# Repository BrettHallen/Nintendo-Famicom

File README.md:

# Nintendo Famicom
Information regarding the Nintendo Family Computer (ニンテンドーファミリーコンピュータ) or Famicom.<br>

## [Dual PPU for Famicom](/ANES_decrazyo)
An implementation of [decrazyo's design](https://github.com/decrazyo/anes) for the NES, creating the Advanced Nintendo Entertainment System or "ANES".

## [Original Schematics](/Archive_Schematics)
Copy of the schematics from [Archive](https://archive.org/details/fc-factory-cpu-schematic-scan).

> Originally from https://forums.nesdev.org/viewtopic.php?t=6950<br>
> Recovered using the Wayback Machine.

> Here is a collection of various schematics for the Nintendo Famicom and related hardware.<br>
> Schematics were pulled from various Japanese sites and dumped onto an Atari themed vintage electronics focused website, however were "lost" when said website went down sometime between late 2017 and early 2018.<br>
> Thankfully, though, they were all backed up onto the Wayback Machine & various other sites, and just took a bit of digging to collect.<br>

> I do not know who the original creators of these schematics are, unfortunately.<br>

I'm informed that the schematics were originally drawn by [Enri](http://cmpslv3.stars.ne.jp).<br>

## [Keyboard (HVC-007)](/Keyboard_HVC-007)
Redesign of the keyboard used with Family BASIC using KiCad.<br>

## [Family BASIC (HVC-BS)](/Family_BASIC_HVC-BS)
Designing cartridge with 8KB RAM.<br>

Also includes a Python script to patch the v3 ROM to allow 8KB of RAM and also fix some bugs.<br>

- [Disassembly](https://github.com/micahcowan/fbdasm)
- [Cartridge schematics](http://cmpslv3.stars.ne.jp/Famic/Fambas.htm)
- [Leaded Solder's investigation](https://www.leadedsolder.com/2025/03/11/family-basic-space-arcade-game-programming.html)

## [3D System (HVC-032)](/3D_System_HVC-032)
Photos & schematic for the controller unit HVC-032.<br>

## [Communication Controller (HVC-051)](/Communication_Controller_HVC-051)
Japanese: 通信コントローラ<br>
Photos & schematic for the Famicom Network controller.<br>

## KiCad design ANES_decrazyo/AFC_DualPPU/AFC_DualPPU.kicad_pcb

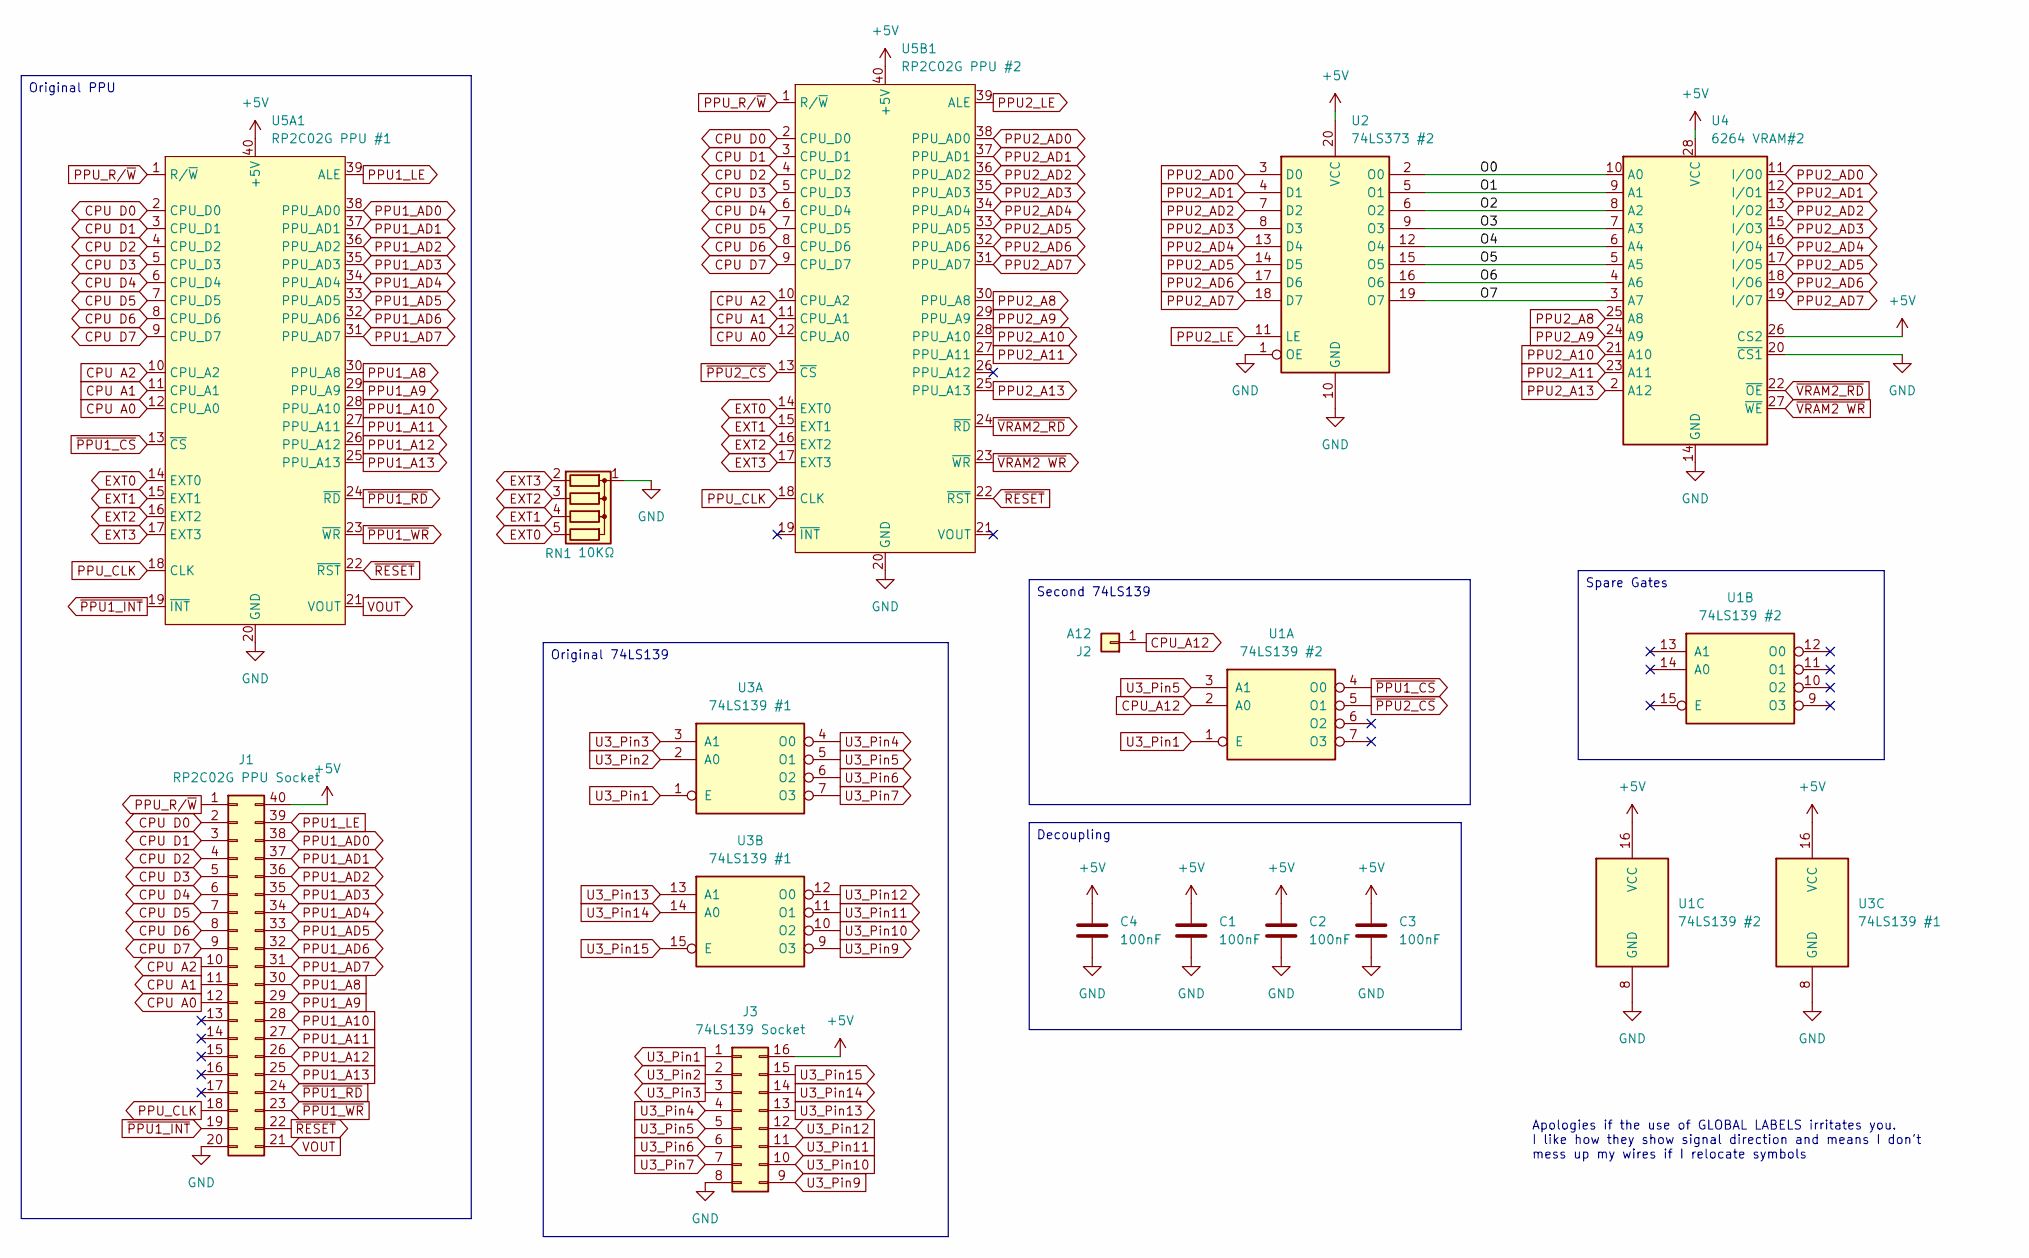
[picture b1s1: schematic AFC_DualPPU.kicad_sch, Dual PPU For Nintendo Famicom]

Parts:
C1, C2, C3, C4: 100nF; C_Disc_D3.4mm_W2.1mm_P2.50mm
J1: RP2C02G PPU Socket; DIP-40_W15.24mm
J2: A12; PinHeader_1x01_P2.54mm_Vertical
J3: 74LS139 Socket; DIP-16_W7.62mm
RN1: 10KΩ; R_Array_SIP5
U1: 74LS139 #2; DIP-16_W7.62mm
U2: 74LS373 #2; DIP-20_W7.62mm
U3: 74LS139 #1; DIP-16_W7.62mm
U4: 6264 VRAM#2; DIP-28_W15.24mm
U5A1: RP2C02G PPU #1; DIP-40_W15.24mm
U5B1: RP2C02G PPU #2; DIP-40_W15.24mm

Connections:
+5V: C1.1, C2.1, C3.1, C4.1, J1.40, J3.16, U1.16 (VCC), U2.20 (VCC), U3.16 (VCC), U4.26 (CS2), U4.28 (VCC), U5A1.40 (+5V), U5B1.40 (+5V)
/O0: U2.2 (O0), U4.10 (A0)
/O1: U2.5 (O1), U4.9 (A1)
/O2: U2.6 (O2), U4.8 (A2)
/O3: U2.9 (O3), U4.7 (A3)
/O4: U2.12 (O4), U4.6 (A4)
/O5: U2.15 (O5), U4.5 (A5)
/O6: U2.16 (O6), U4.4 (A6)
/O7: U2.19 (O7), U4.3 (A7)
CPU A0: J1.12, U5A1.12 (CPU_A0), U5B1.12 (CPU_A0)
CPU A1: J1.11, U5A1.11 (CPU_A1), U5B1.11 (CPU_A1)
CPU A2: J1.10, U5A1.10 (CPU_A2), U5B1.10 (CPU_A2)
CPU D0: J1.2, U5A1.2 (CPU_D0), U5B1.2 (CPU_D0)
CPU D1: J1.3, U5A1.3 (CPU_D1), U5B1.3 (CPU_D1)
CPU D2: J1.4, U5A1.4 (CPU_D2), U5B1.4 (CPU_D2)
CPU D3: J1.5, U5A1.5 (CPU_D3), U5B1.5 (CPU_D3)
CPU D4: J1.6, U5A1.6 (CPU_D4), U5B1.6 (CPU_D4)
CPU D5: J1.7, U5A1.7 (CPU_D5), U5B1.7 (CPU_D5)
CPU D6: J1.8, U5A1.8 (CPU_D6), U5B1.8 (CPU_D6)
CPU D7: J1.9, U5A1.9 (CPU_D7), U5B1.9 (CPU_D7)
CPU_A12: J2.1 (Pin_1_1), U1.2 (A0)
EXT0: RN1.5 (R4), U5A1.14 (EXT0), U5B1.14 (EXT0)
EXT1: RN1.4 (R3), U5A1.15 (EXT1), U5B1.15 (EXT1)
EXT2: RN1.3 (R2), U5A1.16 (EXT2), U5B1.16 (EXT2)
EXT3: RN1.2 (R1), U5A1.17 (EXT3), U5B1.17 (EXT3)
GND: C1.2, C2.2, C3.2, C4.2, J1.20, J3.8, RN1.1 (common), U1.8 (GND), U2.1 (OE), U2.10 (GND), U3.8 (GND), U4.14 (GND), U4.20 (~CS1), U5A1.20 (GND), U5B1.20 (GND)
PPU1_A8: J1.30, U5A1.30 (PPU_A8)
PPU1_A9: J1.29, U5A1.29 (PPU_A9)
PPU1_A10: J1.28, U5A1.28 (PPU_A10)
PPU1_A11: J1.27, U5A1.27 (PPU_A11)
PPU1_A12: J1.26, U5A1.26 (PPU_A12)
PPU1_A13: J1.25, U5A1.25 (PPU_A13)
PPU1_AD0: J1.38, U5A1.38 (PPU_AD0)
PPU1_AD1: J1.37, U5A1.37 (PPU_AD1)
PPU1_AD2: J1.36, U5A1.36 (PPU_AD2)
PPU1_AD3: J1.35, U5A1.35 (PPU_AD3)
PPU1_AD4: J1.34, U5A1.34 (PPU_AD4)
PPU1_AD5: J1.33, U5A1.33 (PPU_AD5)
PPU1_AD6: J1.32, U5A1.32 (PPU_AD6)
PPU1_AD7: J1.31, U5A1.31 (PPU_AD7)
PPU1_LE: J1.39, U5A1.39 (ALE)
PPU2_A8: U4.25 (A8), U5B1.30 (PPU_A8)
PPU2_A9: U4.24 (A9), U5B1.29 (PPU_A9)
PPU2_A10: U4.21 (A10), U5B1.28 (PPU_A10)
PPU2_A11: U4.23 (A11), U5B1.27 (PPU_A11)
PPU2_A13: U4.2 (A12), U5B1.25 (PPU_A13)
PPU2_AD0: U2.3 (D0), U4.11 (I/O0), U5B1.38 (PPU_AD0)
PPU2_AD1: U2.4 (D1), U4.12 (I/O1), U5B1.37 (PPU_AD1)
PPU2_AD2: U2.7 (D2), U4.13 (I/O2), U5B1.36 (PPU_AD2)
PPU2_AD3: U2.8 (D3), U4.15 (I/O3), U5B1.35 (PPU_AD3)
PPU2_AD4: U2.13 (D4), U4.16 (I/O4), U5B1.34 (PPU_AD4)
PPU2_AD5: U2.14 (D5), U4.17 (I/O5), U5B1.33 (PPU_AD5)
PPU2_AD6: U2.17 (D6), U4.18 (I/O6), U5B1.32 (PPU_AD6)
PPU2_AD7: U2.18 (D7), U4.19 (I/O7), U5B1.31 (PPU_AD7)
PPU2_LE: U2.11 (LE), U5B1.39 (ALE)
PPU_CLK: J1.18, U5A1.18 (CLK), U5B1.18 (CLK)
PPU_R/~W: J1.1, U5A1.1 (R/~W), U5B1.1 (R/~W)
U3_Pin1: J3.1, U1.1 (E), U3.1 (E)
U3_Pin2: J3.2, U3.2 (A0)
U3_Pin3: J3.3, U3.3 (A1)
U3_Pin4: J3.4, U3.4 (O0)
U3_Pin5: J3.5, U1.3 (A1), U3.5 (O1)
U3_Pin6: J3.6, U3.6 (O2)
U3_Pin7: J3.7, U3.7 (O3)
U3_Pin9: J3.9, U3.9 (O3)
U3_Pin10: J3.10, U3.10 (O2)
U3_Pin11: J3.11, U3.11 (O1)
U3_Pin12: J3.12, U3.12 (O0)
U3_Pin13: J3.13, U3.13 (A1)
U3_Pin14: J3.14, U3.14 (A0)
U3_Pin15: J3.15, U3.15 (E)
VOUT: J1.21, U5A1.21 (VOUT)
~PPU1_CS: U1.4 (O0), U5A1.13 (~CS)
~PPU1_INT: J1.19, U5A1.19 (~INT)
~PPU1_RD: J1.24, U5A1.24 (~RD)
~PPU1_WR: J1.23, U5A1.23 (~WR)
~PPU2_CS: U1.5 (O1), U5B1.13 (~CS)
~RESET: J1.22, U5A1.22 (~RST), U5B1.22 (~RST)
~VRAM2 WR: U4.27 (~WE), U5B1.23 (~WR)
~VRAM2_RD: U4.22 (~OE), U5B1.24 (~RD)

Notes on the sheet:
Apologies if the use of GLOBAL LABELS irritates you. I like how they show signal direction and means I don't mess up my wires if I relocate symbols
Original 74LS139
Second 74LS139
Decoupling
Spare Gates
Original PPU

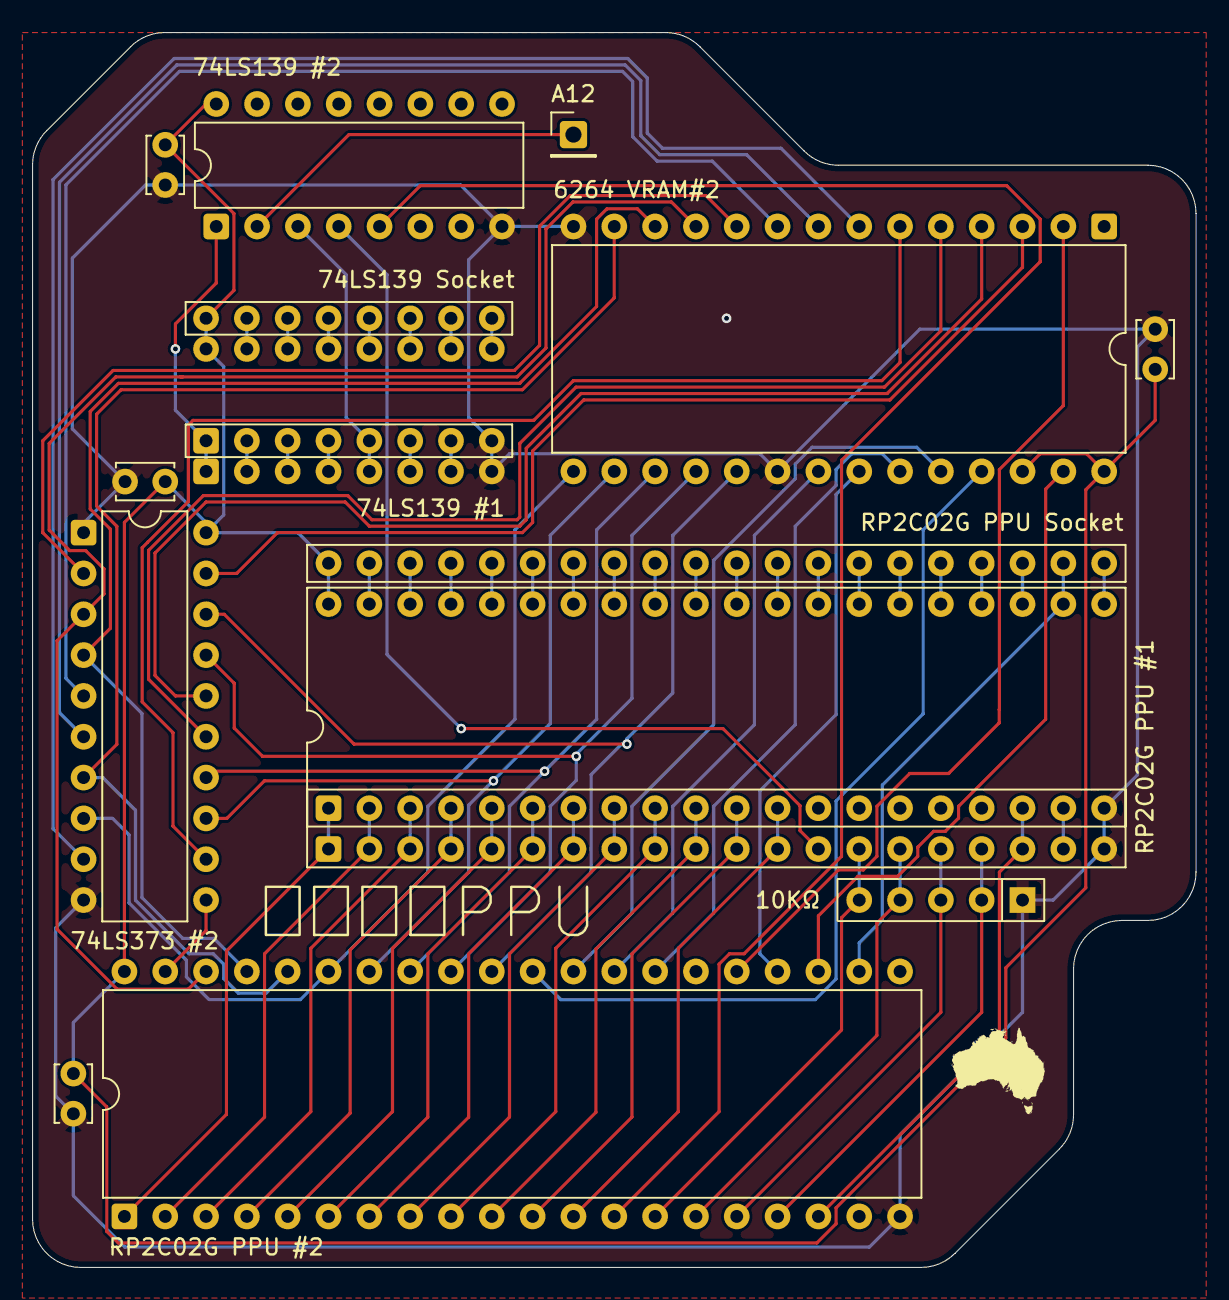
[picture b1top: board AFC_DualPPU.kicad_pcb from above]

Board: 2 copper layers, 72.4 x 76.8 mm, 14 parts (0 on the bottom side), 80 nets.

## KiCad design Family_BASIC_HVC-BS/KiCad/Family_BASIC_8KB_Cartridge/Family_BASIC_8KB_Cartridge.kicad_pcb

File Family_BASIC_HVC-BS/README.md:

# Nintendo Famicom Family BASIC

## Version 0 & 1
These are the original versions for the Famicom.<br>

I don't know much about this but I know [Mr Lurch has done a video](https://youtu.be/f1hPLmRiDNo) with v1.<br>

## Version 2.0A
- PRG: two 16KB (128Kbit) ROMs (RP2D129 0531 and RP2D129 0532) labelled "HVC-FBI-1A" and "HVC-FBI-1B"
- CHR: one 8KB (64Kbit) ROM (RP2D68 0047) labelled "HVC-FB1-0C"
- RAM: 2KB (Fujitsu MB8416A-15-SK)<br>

## Version 2.1A
This is a bugfix version that was available if you returned your v2.0A cartridge.<br>
- PRG: one 32KB (256Kbit) ROM (Fujitsu MB83256) labelled "HVC-FB1-2W"
- CHR: one 8KB (64Kbit) ROM (RP2D70 0032) labelled "HVC-FB1-0C"
- RAM: 2KB (Fujitsu MB8416A-16L-SK)

## Version 3.0
Improved BASIC with double the RAM of v2.<br>
- PRG: one 32KB (256Kbit) ROM (Toshiba TC53257P-1613) labelled "HVC-VT-0W"
- CHR: one 8KB (64Kbit) ROM (M3864-31) labelled "HVC-FB1-0C"
- RAM: 4KB (Toshiba TC5533P-B)

## Adding Support for 8KB RAM
The top of memory is hardcoded to 4KB (in v3.0) so simply replacing the 4KB (32Kbit) RAM won't make any difference - the code needs patching.<br>

There is a [information available](https://github.com/NipponNoraneko/FC-DiskBASIC) about patching v2.1A to mainly add Famicom Disk System (FDS) support, which also increases the RAM to 8KB.  This information mainly concerns itself with creating a Disk BASIC whereas I'm more interested in purely upgrading the cartridge.<br>

This [disassembly of the v3.0 ROM](https://github.com/micahcowan/fbdasm) is invaluable.<br>

So far it looks like these are the required patches in the v3.0 ROM to increase the top of RAM from 0x6FFF (4KB) to 0x7FFF (8KB) - working on verifying the others:<br>
```
   bgGetRam  .eq $6c00  {addr/1024} ; region to save bg data with BGGET
   memoryTop .eq $6fff              ; What FRETOP is set to by default

PATCH0: lda #>memoryTop
06A4: 6F -> 7F

PATCH1: cmp #$70 ;arg >= #$7000?
17D8: 70 -> 80

PATCH2: lda #(>memoryTop)+1
2DC9: 70 -> 80

PATCH3: cmp #>bgGetRam ;is there room after program for BG data?
31BE: 6C -> 7C     

PATCH4: lda #>bgGetRam
31CB: 6C -> 7C

PATCH5: lda #>bgGetRam
320C: 6C -> 7C
```

I am working on a Python script to make this patching of the binary ROM simple:<br>
```
% python3 fb_rom_patcher.py Family_BASIC_v30_PRG_CHR.NES

#############################################
# Brett's Nintendo Family BASIC ROM patcher #
# for 8KB RAM Support (Jan 2026)            #
#############################################

>> Input ROM checksum: 0x6BA08175
>> Detected: Family BASIC v3.0 (PRG+CHR+NES 2.0 header)

>> Applying single-byte patches:
Patching 0x000A: 0x60 → 0x70 [NES 2.0 header 4KB->8KB]
Patching 0x06B4: 0x6F → 0x7F [Increase RAM limit from 0x6C00 to 0x7C00]
Patching 0x17E8: 0x70 → 0x80 [Increase RAM limit from 0x6C00 to 0x7C00]
Patching 0x2DD9: 0x70 → 0x80 [Increase RAM limit from 0x6C00 to 0x7C00]
Patching 0x31CE: 0x6C → 0x7C [Increase RAM limit from 0x6C00 to 0x7C00]
Patching 0x31DB: 0x6C → 0x7C [Increase RAM limit from 0x6C00 to 0x7C00]
Patching 0x321C: 0x6C → 0x7C [Increase RAM limit from 0x6C00 to 0x7C00]
Patching 0x133E: 0xA0 → 0xA9 [REM statement bug fix]
Patching 0x4F99: 0x30 → 0x31 [Version change to v3.1]

>> Applying multi-byte patches:
Patching 0x0CAD: 0xA5 → 0xA5 [RENUM command bug fix]
Patching 0x0CAE: 0x7D → 0x7C [RENUM command bug fix]
Patching 0x0CAF: 0xC5 → 0x38 [RENUM command bug fix]
Patching 0x0CB0: 0x7F → 0xE5 [RENUM command bug fix]
Patching 0x0CB1: 0xF0 → 0x7E [RENUM command bug fix]
Patching 0x0CB2: 0x02 → 0xA5 [RENUM command bug fix]
Patching 0x0CB3: 0xB0 → 0x7D [RENUM command bug fix]
Patching 0x0CB4: 0x0C → 0xE5 [RENUM command bug fix]
Patching 0x0CB5: 0xA5 → 0x7F [RENUM command bug fix]
Patching 0x0CB6: 0x7C → 0xB0 [RENUM command bug fix]
Patching 0x0CB7: 0xC5 → 0x09 [RENUM command bug fix]
Patching 0x0CB8: 0x7E → 0x4C [RENUM command bug fix]
Patching 0x0CB9: 0xB0 → 0xAB [RENUM command bug fix]
Patching 0x0CBA: 0x06 → 0x8C [RENUM command bug fix]
Patching 0x0E52: 0x10 → 0x30 [-32768-0 overflow error bug fix]
Patching 0x0E53: 0x06 → 0x04 [-32768-0 overflow error bug fix]

>> Patched ROM saved as: Family_BASIC_v30_PRG_CHR_patched.NES
>> Patched ROM checksum: 0xEFDACFF8
>> SUCCESS: Checksum verified
```

## NES 2.0 Headers
Required to be prepended to the combined PRG+CHR ROM image to run in an emulator.<br>
I've added what *I think* are the correct NES 2.0 headers to my ROMs, and the CRC32 checksum calculation my script checks assumes these.<br>
```
% python3 nes_header_read.py Family_BASIC_v30_PRG_CHR.NES 

#################################
# Brett's NES Header Reader     #
# Work in progress, 14/JAN/2026 #
#################################

Format ............................ NES 2.0
Vs. System PPU variant ............ 0
Vs. System hardware/protection .... 0
PRG-ROM size ...................... 32768 bytes
CHR-ROM size ...................... 8192 bytes
PRG-RAM (volatile) size ........... 0 bytes
PRG-NVRAM (battery-backed) size ... 4096 bytes
CHR-RAM (volatile) size ........... 0 bytes
CHR-NVRAM (battery-backed) size ... 0 bytes
Mapper ............................ 0 (NROM)
Submapper ......................... 0
Mirroring ......................... Vertical
Battery-backed .................... True
Trainer ........................... False
Four-screen VRAM .................. False
VS Unisystem ...................... False
PlayChoice-10 ..................... False
CPU/PPU Timing .................... RP2C02 (NTSC NES)
Default expansion device .......... Family BASIC Keyboard plus Famicom Data Recorder
```

If yours are different and my script rejects your .NES file, just modify the script with the checksum it calculates for your file!<br>
```
KNOWN_CRCS = {
    "FBv10":        (0x868FCD89, 0x00000000), # no 8KB patch planned
    "FBv10_merge":  (0xF7DB8B5C, 0x00000000), # no 8KB patch planned
    "FBv10_NES":    (0x30B1840A, 0x00000000), # no 8KB patch planned
    "FBv20A_merge": (0xF7606810, 0x00000000), # no 8KB patch planned
    "FBv20A_NES2":  (0x300A6746, 0x00000000), # no 8KB patch planned
    "FBv21A":       (0xDE34526E, 0x85BDD21B), # PRG
    "FBv21A_merge": (0x895037BC, 0x72C38E25), # PRG+CHR
    "FBv21A_NES2":  (0x4E3A38EA, 0x3D43C6D0), # PRG+CHR+NES header
    "FBv30":        (0x3AAEED3F, 0xC7FD9017), # PRG
    "FBv30_merge":  (0xB2530AFC, 0x933709F7), # PRG+CHR
    "FBv30_NES2":   (0x6BA08175, 0xEFDACFF8), # PRG+CHR+NES header
    "FB_CHR":       (0x11848B93, 0x00000000)  # CHR
}
```
The checksum for the raw ROM files *should* be correct.<br>

- Family BASIC v2.1 2KB header: 4E 45 53 1A 02 01 03 08 00 00 50 00 00 00 00 23
- Family BASIC v2.1 8KB header: 4E 45 53 1A 02 01 03 08 00 00 70 00 00 00 00 23 (?)
- Family BASIC v3.0 4KB header: 4E 45 53 1A 02 01 03 08 00 00 60 00 00 00 00 23
- Family BASIC v3.0 8KB header: 4E 45 53 1A 02 01 03 08 00 00 70 00 00 00 00 23 (?)

## Version 3.0 Bugfixes
There are [several bugs](https://github.com/micahcowan/fbdasm/blob/main/BUGS.md) in v3 that have been identified.<br>

### [REM Comments Corrupted by Katakana Small Yo (ョ)](https://github.com/micahcowan/fbdasm/blob/main/BUGS.md#rem-comments-corrupted-by-katakana-small-yo-ョ) 
As noted by Micah in his [annotated disassembly](https://famibe.addictivecode.org/disassembly/fb3.nes.html):<br>
Original fault - キョートー　becomes キートー
```
932E: A0 00        TokRemCopyToEnd LDY     #$00                    ;BUG: this should be lda
9330: 85 99                        STA     zpToken                 ;...or else this should be sty
9332: 4C C2 92                     JMP     TokCopyUntilTok
```

Possible fix
```
932E: A9 00        TokRemCopyToEnd LDA     #$00                    ;LDY -> LDA
9330: 85 99                        STA     zpToken
9332: 4C C2 92                     JMP     TokCopyUntilTok
```

### [RENUM Can Create Duplicate Line Numbers](https://github.com/micahcowan/fbdasm/blob/main/BUGS.md#renum-can-create-duplicate-line-numbers)
Original fault
```
                   RENUM_checkNewGeOld
8C9D: A5 7D                        LDA     vZpNewStartLNum+1
8C9F: C5 7F                        CMP     vZpOldStartLNum+1
8CA1: F0 02                        BEQ     @cmpLo              ;is new start lnum (hi byte) > old start lnum (hi byte)?
8CA3: B0 0C                        BCS     RENUM_argsDone      ;yes -> everything's great
8CA5: A5 7C        @cmpLo          LDA     vZpNewStartLNum     ;else, is new start lnum (lo byte) >= old start lnum (lo byte)?
8CA7: C5 7E                        CMP     vZpOldStartLNum     ;BUG! Permits high byte lower, as long as low byte is higher!
8CA9: B0 06                        BCS     RENUM_argsDone      ; This can result in repeated line numbers, and/or lower coming after higher
8CAB: 4C 94 84                     JMP     ErrorIllegalValue
```

Possible fix - treat line numbers as 16-bit numbers:
```
                   RENUM_checkNewGeOld
8C9D: A5 7C                        LDA     vZpNewStartLNum     ; Load new low byte
8C9F: 38                           SEC                         ; Set carry for subtraction
8CA0: E5 7E                        SBC     vZpOldStartLNum     ; Subtract old low byte
8CA2: A5 7D                        LDA     vZpNewStartLNum+1   ; Load new high byte
8CA4: E5 7F                        SBC     vZpOldStartLNum+1   ; Subtract old high byte (with borrow)
8CA6: B0 09                        BCS     RENUM_argsDone      ; If carry set (new >= old), good –> jump to $8CB1
8CA8: 4C AB 8C                     JMP     $8CAB               ; Else error (Illegal quantity at $8CAB)
8CAB: 4C 94 84                     JMP     ErrorIllegalValue
```
(replace $8CA8 with 3xNOP and let it fall through to $8CAB?)

### [Overflow When Subtracting Zero](https://github.com/micahcowan/fbdasm/blob/main/BUGS.md#overflow-when-subtracting-zero)
Incorrect overflow (OV) error is raised when -32768-0 is executed.<br>
```
                   Sub_WAccumIs32768
8E40: A5 2D                        LDA     zpWParam+1
8E42: 10 06                        BPL     @errOverfl     ;BUG: produces OV ERROR even if WParam is zero lol
8E44: 20 FD 8D                     JSR     WParamNegate
8E47: 4C AC 8E                     JMP     Add
8E4A: 4C F2 8E     @errOverfl      JMP     ErrorOverflow
```

Possible fix - raise overflow error only when subtracting positive number (>0)
```
                   Sub_WAccumIs32768
8E40: A5 2D                        LDA     zpWParam+1
8E42: 30 04                        BMI     continue       ;if subtracting negative number, safe -> negate & add
8E44: 20 FD 8D                     JSR     WParamNegate
8E47: 4C AC 8E     continue        JMP     Add
8E4A: 4C F2 8E     @errOverfl      JMP     ErrorOverflow
```

- If subtracting negative number ... correct (negate then add)
- If subtracting zero ... doesn't branch ... falls through to Add
- If subtracting positive number... falls through to ErrorOverflow

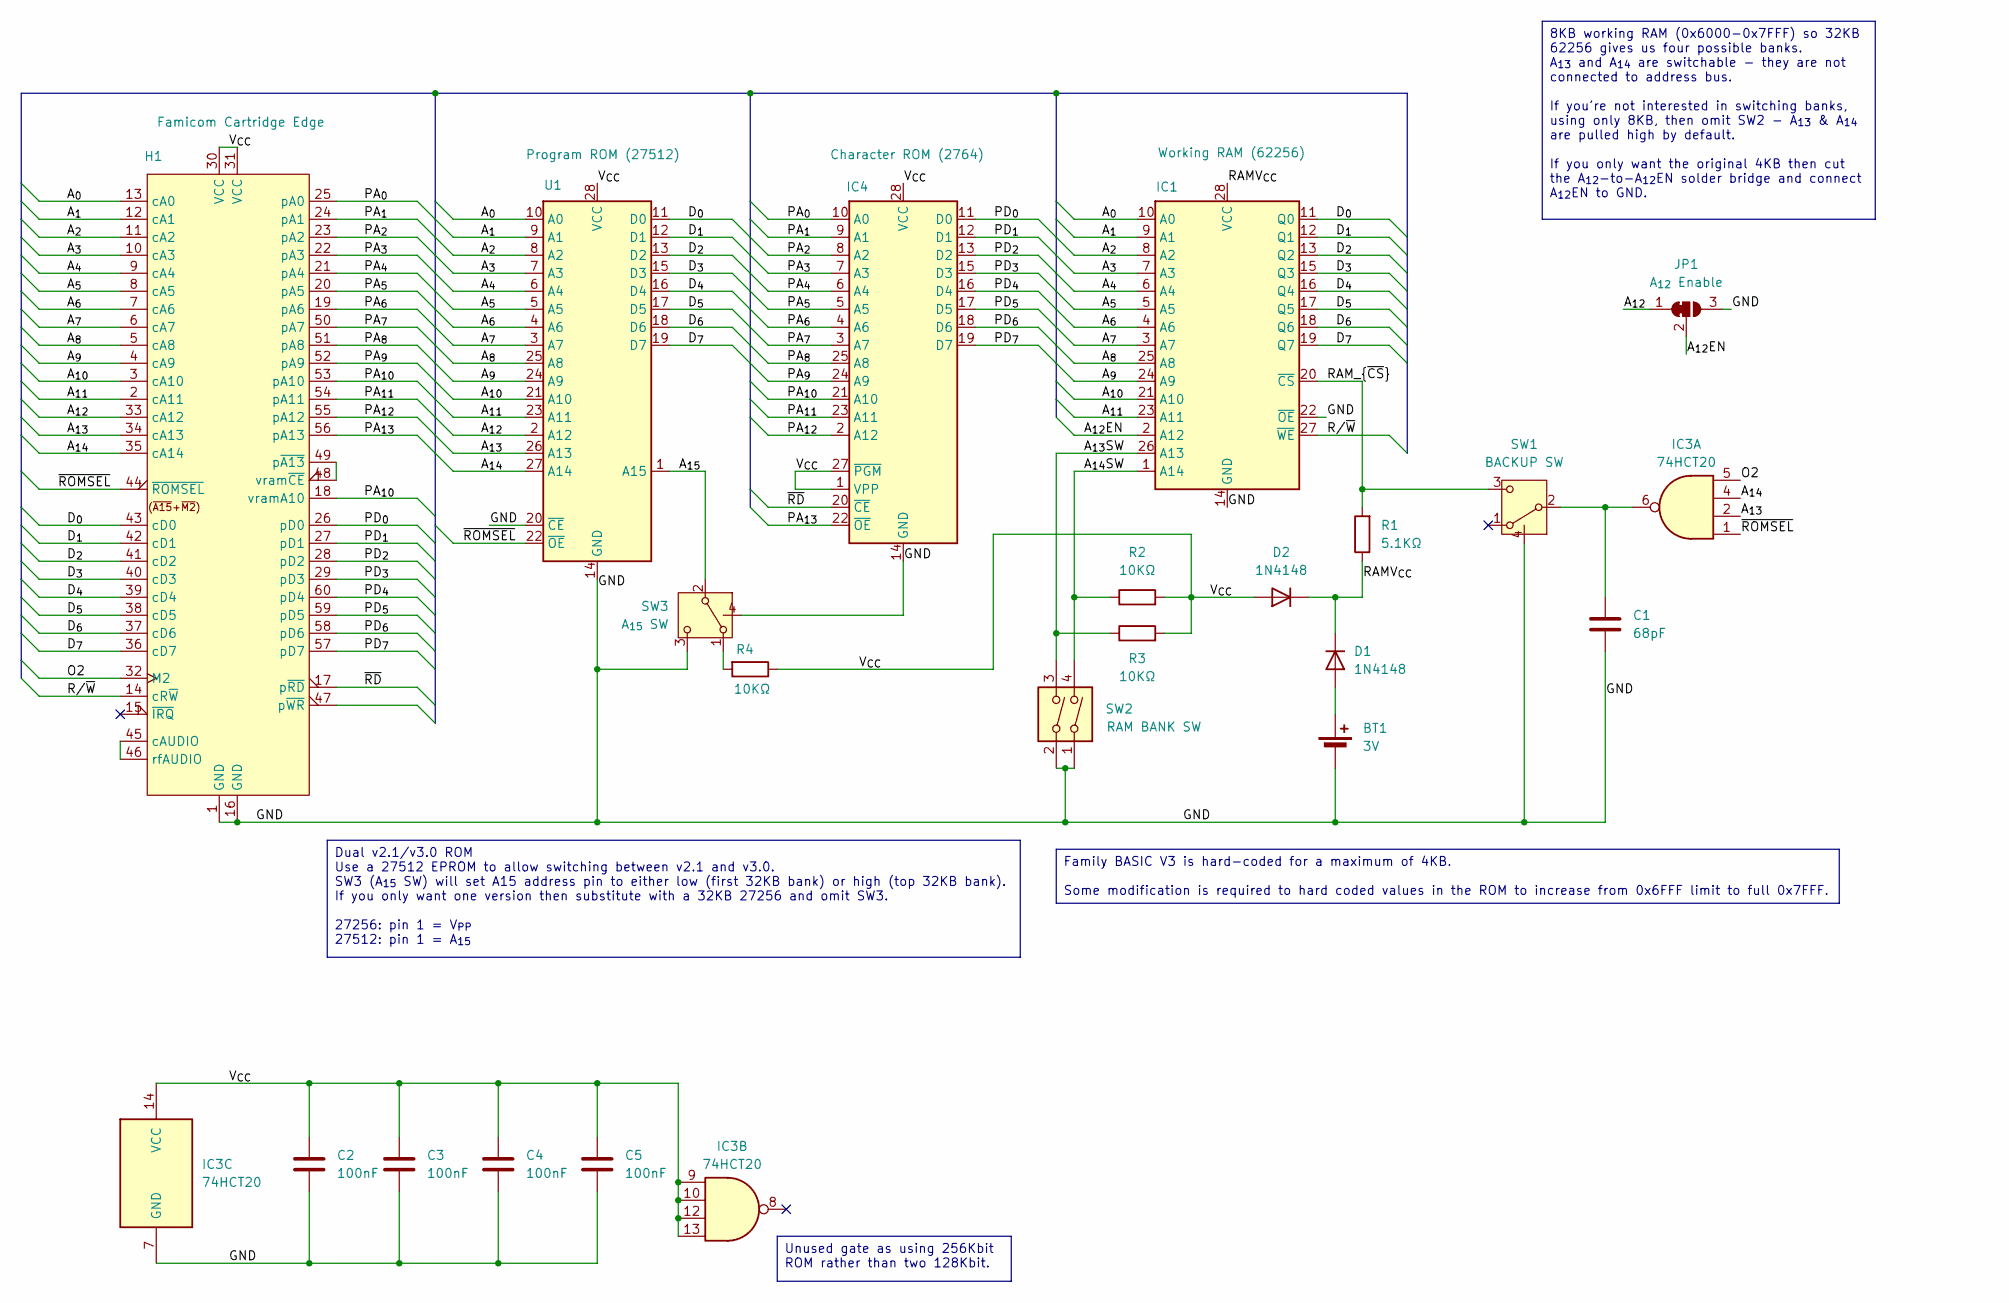
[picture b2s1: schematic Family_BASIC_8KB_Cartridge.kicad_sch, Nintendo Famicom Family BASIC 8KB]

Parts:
BT1: 3V; 3000
C1: 68pF; C_Axial_L3.8mm_D2.6mm_P7.50mm_Horizontal
C2, C3, C4, C5: 100nF; C_Axial_L3.8mm_D2.6mm_P7.50mm_Horizontal
D1, D2: 1N4148; D_DO-35_SOD27_P7.62mm_Horizontal
H1: Famicom Cartridge Edge; Famicom_Cartridge_Edge_Connector_(long_legs)
IC1: Working RAM (62256); DIP-28_W15.24mm
IC3: 74HCT20; DIP-14_W7.62mm
IC4: Character ROM (2764); DIP-28_W15.24mm
JP1: A_{12} Enable; SolderJumper-3_P1.3mm_Bridged12_RoundedPad1.0x1.5mm
R1: 5.1KΩ; R_Axial_DIN0207_L6.3mm_D2.5mm_P7.62mm_Horizontal
R2, R3, R4: 10KΩ; R_Axial_DIN0207_L6.3mm_D2.5mm_P7.62mm_Horizontal
SW1: BACKUP SW; SW_E-Switch_EG1224_SPDT_Angled
SW2: RAM BANK SW; SW_DIP_SPSTx02_Slide_9.78x7.26mm_W7.62mm_P2.54mm
SW3: A_{15} SW; SW_E-Switch_EG1224_SPDT_Angled
U1: Program ROM (27512); DIP-28_W15.24mm

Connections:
/A_{0}: H1.13 (cA0), IC1.10 (A0), U1.10 (A0)
/A_{1}: H1.12 (cA1), IC1.9 (A1), U1.9 (A1)
/A_{2}: H1.11 (cA2), IC1.8 (A2), U1.8 (A2)
/A_{3}: H1.10 (cA3), IC1.7 (A3), U1.7 (A3)
/A_{4}: H1.9 (cA4), IC1.6 (A4), U1.6 (A4)
/A_{5}: H1.8 (cA5), IC1.5 (A5), U1.5 (A5)
/A_{6}: H1.7 (cA6), IC1.4 (A6), U1.4 (A6)
/A_{7}: H1.6 (cA7), IC1.3 (A7), U1.3 (A7)
/A_{8}: H1.5 (cA8), IC1.25 (A8), U1.25 (A8)
/A_{9}: H1.4 (cA9), IC1.24 (A9), U1.24 (A9)
/A_{10}: H1.3 (cA10), IC1.21 (A10), U1.21 (A10)
/A_{11}: H1.2 (cA11), IC1.23 (A11), U1.23 (A11)
/A_{12}: H1.33 (cA12), JP1.1 (A), U1.2 (A12)
/A_{12}EN: IC1.2 (A12), JP1.2 (C)
/A_{13}: H1.34 (cA13), IC3.2, U1.26 (A13)
/A_{13}SW: IC1.26 (A13), R3.1, SW2.3
/A_{14}: H1.35 (cA14), IC3.4, U1.27 (A14)
/A_{14}SW: IC1.1 (A14), R2.1, SW2.4
/A_{15}: SW3.2 (B), U1.1 (A15)
/D_{0}: H1.43 (cD0), IC1.11 (Q0), U1.11 (D0)
/D_{1}: H1.42 (cD1), IC1.12 (Q1), U1.12 (D1)
/D_{2}: H1.41 (cD2), IC1.13 (Q2), U1.13 (D2)
/D_{3}: H1.40 (cD3), IC1.15 (Q3), U1.15 (D3)
/D_{4}: H1.39 (cD4), IC1.16 (Q4), U1.16 (D4)
/D_{5}: H1.38 (cD5), IC1.17 (Q5), U1.17 (D5)
/D_{6}: H1.37 (cD6), IC1.18 (Q6), U1.18 (D6)
/D_{7}: H1.36 (cD7), IC1.19 (Q7), U1.19 (D7)
/GND: BT1.3 (-), C1.2, C2.2, C3.2, C4.2, C5.2, H1.1 (GND), H1.16 (GND), IC1.14 (GND), IC1.22 (~OE), IC3.7 (GND), IC4.14 (GND), JP1.3 (B), SW1.4 (GND), SW2.1, SW2.2, SW3.3 (C), SW3.4 (GND), U1.14 (GND), U1.20 (~CE)
/O2: H1.32 (M2), IC3.5
/PA_{0}: H1.25 (pA0), IC4.10 (A0)
/PA_{1}: H1.24 (pA1), IC4.9 (A1)
/PA_{2}: H1.23 (pA2), IC4.8 (A2)
/PA_{3}: H1.22 (pA3), IC4.7 (A3)
/PA_{4}: H1.21 (pA4), IC4.6 (A4)
/PA_{5}: H1.20 (pA5), IC4.5 (A5)
/PA_{6}: H1.19 (pA6), IC4.4 (A6)
/PA_{7}: H1.50 (pA7), IC4.3 (A7)
/PA_{8}: H1.51 (pA8), IC4.25 (A8)
/PA_{9}: H1.52 (pA9), IC4.24 (A9)
/PA_{10}: H1.18 (vramA10), H1.53 (pA10), IC4.21 (A10)
/PA_{11}: H1.54 (pA11), IC4.23 (A11)
/PA_{12}: H1.55 (pA12), IC4.2 (A12)
/PA_{13}: H1.56 (pA13), IC4.22 (~OE)
/PD_{0}: H1.26 (pD0), IC4.11 (D0)
/PD_{1}: H1.27 (pD1), IC4.12 (D1)
/PD_{2}: H1.28 (pD2), IC4.13 (D2)
/PD_{3}: H1.29 (pD3), IC4.15 (D3)
/PD_{4}: H1.60 (pD4), IC4.16 (D4)
/PD_{5}: H1.59 (pD5), IC4.17 (D5)
/PD_{6}: H1.58 (pD6), IC4.18 (D6)
/PD_{7}: H1.57 (pD7), IC4.19 (D7)
/RAMV_{CC}: D1.1 (K), D2.1 (K), IC1.28 (VCC), R1.1
/RAM_{~CS}: IC1.20 (~CS), R1.2, SW1.3 (C)
/R/~W: H1.14 (cR~W), IC1.27 (~WE)
/V_{CC}: C2.1, C3.1, C4.1, C5.1, D2.2 (A), H1.30 (VCC), H1.31 (VCC), IC3.9, IC3.10, IC3.12, IC3.13, IC3.14 (VCC), IC4.1 (VPP), IC4.27 (~PGM), IC4.28 (VCC), R2.2, R3.2, R4.1, U1.28 (VCC)
/~RD: H1.17 (p~RD), IC4.20 (~CE)
/~ROMSEL: H1.44 (~ROMSEL), IC3.1, U1.22 (~OE)
unnamed: BT1.1 (+), D1.2 (A)
unnamed: H1.45 (cAUDIO), H1.46 (rfAUDIO)
unnamed: H1.48 (vram~CE), H1.49 (p~A13)
unnamed: C1.1, IC3.6, SW1.2 (B)
unnamed: R4.2, SW3.1 (A)

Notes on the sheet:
Dual v2.1/v3.0 ROM Use a 27512 EPROM to allow switching between v2.1 and v3.0. SW3 (A_{15} SW) will set A15 address pin to either low (first 32KB bank) or high (top 32KB bank). If you only want one version then substitute with a 32KB 27256 and omit SW3. 27256: pin 1 = V_{PP} 27512: pin 1 = A_{15}
Unused gate as using 256Kbit ROM rather than two 128Kbit.
8KB working RAM (0x6000-0x7FFF) so 32KB 62256 gives us four possible banks. A_{13} and A_{14} are switchable - they are not connected to address bus. If you're not interested in switching banks, using only 8KB, then omit SW2 - A_{13} & A_{14} are pulled high by default. If you only want the origina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
Family BASIC V3 is hard-coded for a maximum of 4KB. Some modification is required to hard coded values in the ROM to increase from 0x6FFF limit to full 0x7FFF.

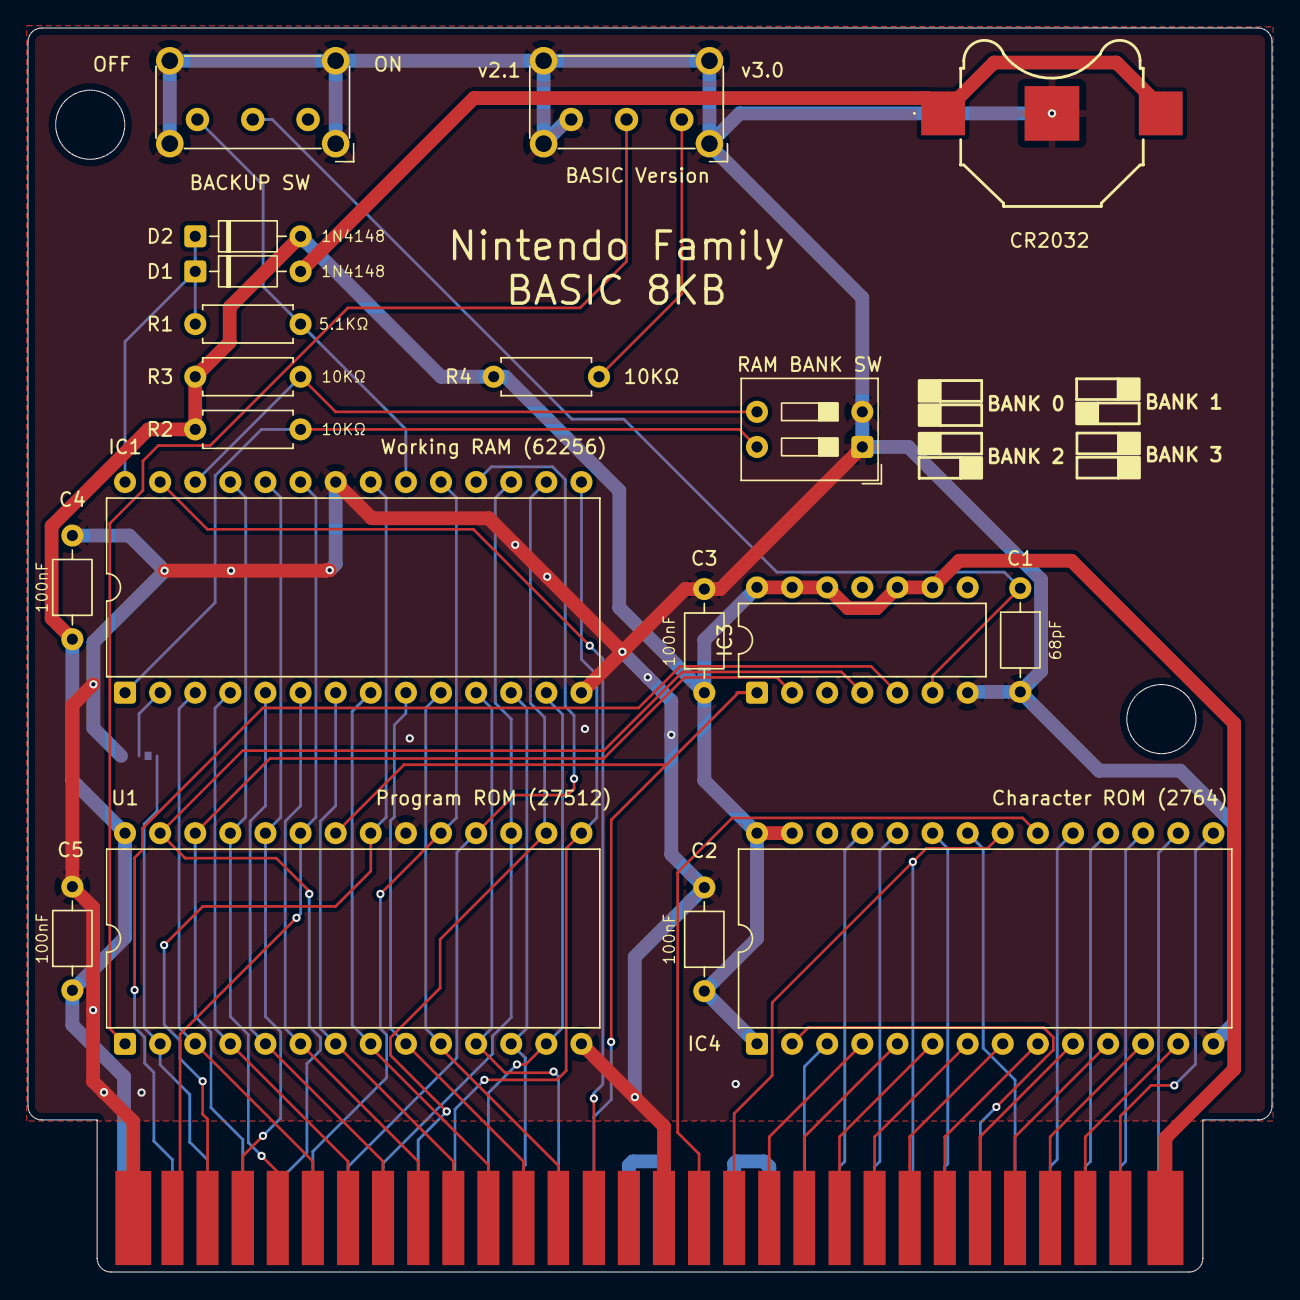
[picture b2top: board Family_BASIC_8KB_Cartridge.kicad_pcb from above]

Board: 2 copper layers, 90.0 x 90.0 mm, 21 parts (1 on the bottom side), 62 nets.

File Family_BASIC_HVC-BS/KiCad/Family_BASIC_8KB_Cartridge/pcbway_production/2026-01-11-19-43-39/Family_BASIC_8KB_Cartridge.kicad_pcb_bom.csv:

Designator,Quantity,Value,Footprint,Package,MPN,DNP,Mount_Type,Description,Sim.Device,Sim.Pins
BT1,1,3V,3000,,,,smt,Single-cell battery,,
C1,1,68pF,C_Axial_L3.8mm_D2.6mm_P7.50mm_Horizontal,,,,tht,Unpolarized capacitor,,
"C2, C3, C4, C5",4,100nF,C_Axial_L3.8mm_D2.6mm_P7.50mm_Horizontal,,,,tht,Unpolarized capacitor,,
"D1, D2",2,1N4148,D_DO-35_SOD27_P7.62mm_Horizontal,,,,tht,Diode,D,1=K 2=A
H1,1,Famicom Cartridge Edge,Famicom_Cartridge_Edge_Connector_(long_legs),,,,smt,,,
IC1,1,Working RAM (62256),DIP-28_W15.24mm,,,,tht,"32,768-word × 8-bit High Speed CMOS Static RAM, 70ns, DIP-28",,
IC3,1,74HCT20,DIP-14_W7.62mm,,,,tht,Dual 4-input NAND,,
IC4,1,Character ROM (2764),DIP-28_W15.24mm,,,,tht,"OTP EPROM 64 KiBit, [Obsolete 2004-01]",,
R1,1,5.1KΩ,R_Axial_DIN0207_L6.3mm_D2.5mm_P7.62mm_Horizontal,,,,tht,Resistor,,
"R2, R3, R4",3,10KΩ,R_Axial_DIN0207_L6.3mm_D2.5mm_P7.62mm_Horizontal,,,,tht,Resistor,,
SW1,1,BACKUP SW,SW_E-Switch_EG1224_SPDT_Angled,,,,tht,"Switch, single pole double throw",,
SW2,1,RAM BANK SW,SW_DIP_SPSTx02_Slide_9.78x7.26mm_W7.62mm_P2.54mm,,,,tht,"2x DIP Switch, Single Pole Single Throw (SPST) switch, small symbol",,
SW3,1,A_{15} SW,SW_E-Switch_EG1224_SPDT_Angled,,,,tht,"Switch, single pole double throw",,
U1,1,Program ROM (27512),DIP-28_W15.24mm,,,,tht,OTP EPROM 512 KiBit,,

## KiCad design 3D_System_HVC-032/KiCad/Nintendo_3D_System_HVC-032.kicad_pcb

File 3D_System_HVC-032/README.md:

# 3D System (3DS) HVC-032

## [KiCad](/3D_System_HVC-032/KiCad)
Schematic of the 3DS controller box in KiCad.<br>

The controller uses a custom Sharp IX0043 chip.<br>

Its functionality could perhaps be replacated by an Atmega328.<br>

## [Logic Analyser](/3D_System_HVC-032/Logic_Analyser)
Capture of the controller signalling.  <br>

You can use the Saleaea Logic 2 software [(free download, no need to have the hardware)](https://saleae.com) to open the .SAL capture file.

## [Home Brew Controller](/3D_System_HVC-032/HOME-brewed_Control_Circuit)
Controller design from 1993 to use the similar Sega Master System (SMS) 3D glasses on a PC.<br>

I've not finished re-drawing in KiCad yet (11/Jan/2026).<br>

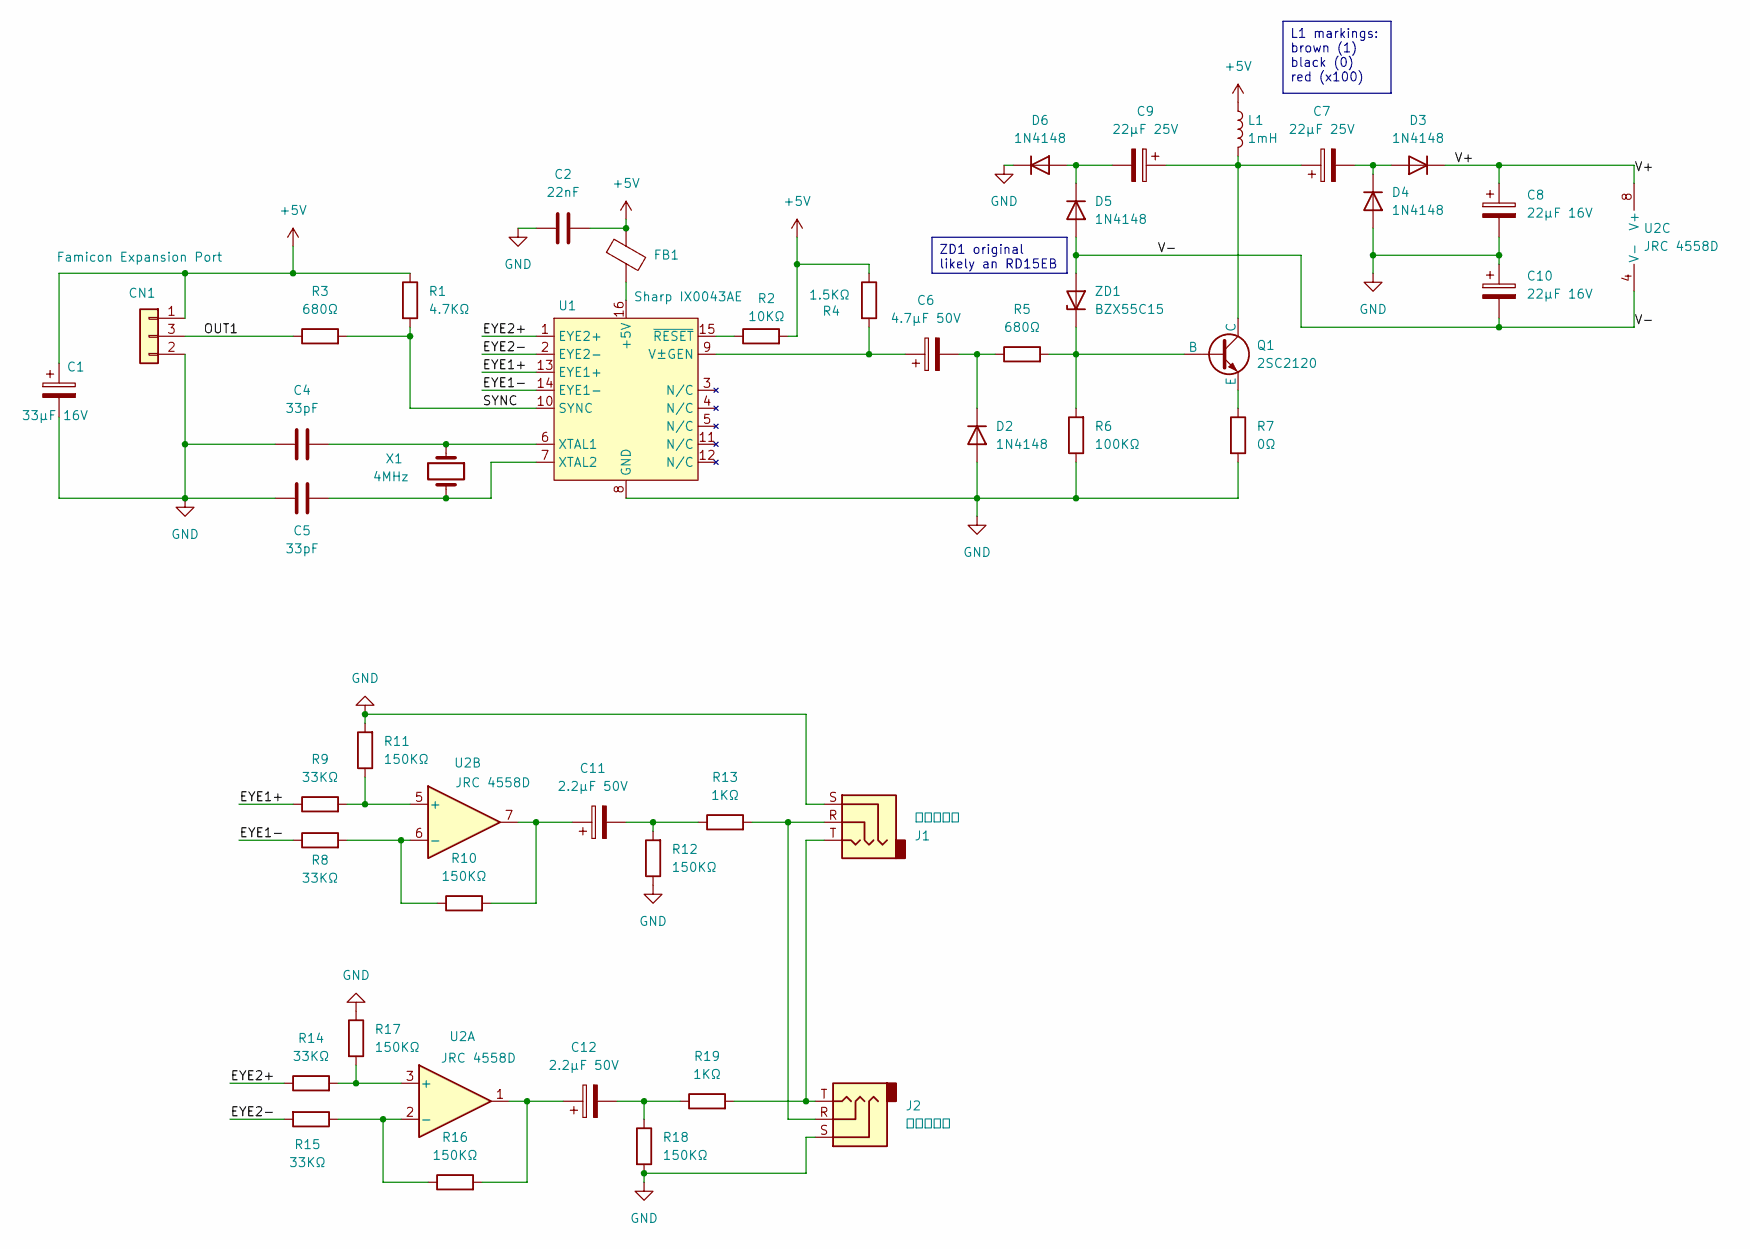
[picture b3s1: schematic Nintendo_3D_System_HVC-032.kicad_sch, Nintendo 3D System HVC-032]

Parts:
C1: 33µF 16V; CP_Radial_D5.0mm_P2.50mm
C2: 22nF; C_Disc_D3.4mm_W2.1mm_P2.50mm
C4, C5: 33pF; C_Disc_D3.4mm_W2.1mm_P2.50mm
C6: 4.7µF 50V; CP_Radial_D5.0mm_P2.50mm
C7, C9: 22µF 25V; CP_Radial_D5.0mm_P2.50mm
C8, C10: 22µF 16V; CP_Radial_D5.0mm_P2.50mm
C11, C12: 2.2µF 50V; CP_Radial_D5.0mm_P2.50mm
CN1: Famicon Expansion Port; PinHeader_1x03_P2.54mm_Vertical
D2, D3, D4, D5, D6: 1N4148; D_DO-35_SOD27_P7.62mm_Horizontal
FB1: FerriteBead; FB_28L0138-10R-10
J1: スコープ１; Jack_3.5mm_CUI_SJ1-3513N_Horizontal
J2: スコープ２; Jack_3.5mm_CUI_SJ1-3513N_Horizontal
L1: 1mH; L_Axial_L16.0mm_D7.5mm_P25.40mm_Horizontal_Fastron_XHBCC
Q1: 2SC2120; TO-92_Inline
R1: 4.7KΩ; R_Axial_DIN0207_L6.3mm_D2.5mm_P7.62mm_Horizontal
R2: 10KΩ; R_Axial_DIN0207_L6.3mm_D2.5mm_P7.62mm_Horizontal
R3, R5: 680Ω; R_Axial_DIN0207_L6.3mm_D2.5mm_P7.62mm_Horizontal
R4: 1.5KΩ; R_Axial_DIN0207_L6.3mm_D2.5mm_P7.62mm_Horizontal
R6: 100KΩ; R_Axial_DIN0207_L6.3mm_D2.5mm_P7.62mm_Horizontal
R7: 0Ω; R_Axial_DIN0207_L6.3mm_D2.5mm_P7.62mm_Horizontal
R8, R9, R14, R15: 33KΩ; R_Axial_DIN0207_L6.3mm_D2.5mm_P7.62mm_Horizontal
R10, R11, R12, R16, R17, R18: 150KΩ; R_Axial_DIN0207_L6.3mm_D2.5mm_P7.62mm_Horizontal
R13, R19: 1KΩ; R_Axial_DIN0207_L6.3mm_D2.5mm_P7.62mm_Horizontal
U1: Sharp IX0043AE; DIP-16_W7.62mm
U2: JRC 4558D; DIP-8_W7.62mm
X1: 4MHz; Crystal_HC49-U_Vertical
ZD1: BZX55C15; D_DO-35_SOD27_P7.62mm_Horizontal

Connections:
+5V: C1.1, C2.2, CN1.1, FB1.1, L1.1, R1.1, R2.2, R4.1
/EYE1+: R9.1, U1.13 (EYE1+)
/EYE1-: R8.1, U1.14 (EYE1-)
/EYE2+: R14.1, U1.1 (EYE2+)
/EYE2-: R15.2, U1.2 (EYE2-)
/OUT1: CN1.3, R3.1
/SYNC: R1.2, R3.2, U1.10 (SYNC)
/V+: C8.1, D3.1 (K), U2.8 (V+)
/V-: C10.2, D5.2 (A), U2.4 (V-), ZD1.2 (A)
GND: C1.2, C2.1, C4.1, C5.1, C8.2, C10.1, CN1.2, D2.2 (A), D4.2 (A), D6.1 (K), J1.S, J2.S, R6.1, R7.2, R11.2, R12.1, R17.1, R18.2, U1.8 (GND)
unnamed: C11.1, R10.2, U2.7
unnamed: C11.2, R12.2, R13.1
unnamed: C12.1, R16.2, U2.1
unnamed: C12.2, R18.1, R19.1
unnamed: C6.2, D2.1 (K), R5.1
unnamed: C7.2, D3.2 (A), D4.1 (K)
unnamed: C9.2, D5.1 (K), D6.2 (A)
unnamed: J1.R, J2.R, R13.2
unnamed: J1.T, J2.T, R19.2
unnamed: Q1.2 (B), R5.2, R6.2, ZD1.1 (K)
unnamed: C7.1, C9.1, L1.2, Q1.1 (C)
unnamed: Q1.3 (E), R7.1
unnamed: FB1.2, U1.16 (+5V)
unnamed: C6.1, R4.2, U1.9 (V±GEN)
unnamed: C4.2, U1.6 (XTAL1), X1.1
unnamed: C5.2, U1.7 (XTAL2), X1.2
unnamed: R2.1, U1.15 (~RESET)
unnamed: R14.2, R17.2, U2.3 (+)
unnamed: R15.1, R16.1, U2.2 (-)
unnamed: R9.2, R11.1, U2.5 (+)
unnamed: R8.2, R10.1, U2.6 (-)

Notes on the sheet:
L1 markings: brown (1) black (0) red (x100)
ZD1 original likely an RD15EB

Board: 2 copper layers, 45 parts (0 on the bottom side), 31 nets, no tracks yet.
